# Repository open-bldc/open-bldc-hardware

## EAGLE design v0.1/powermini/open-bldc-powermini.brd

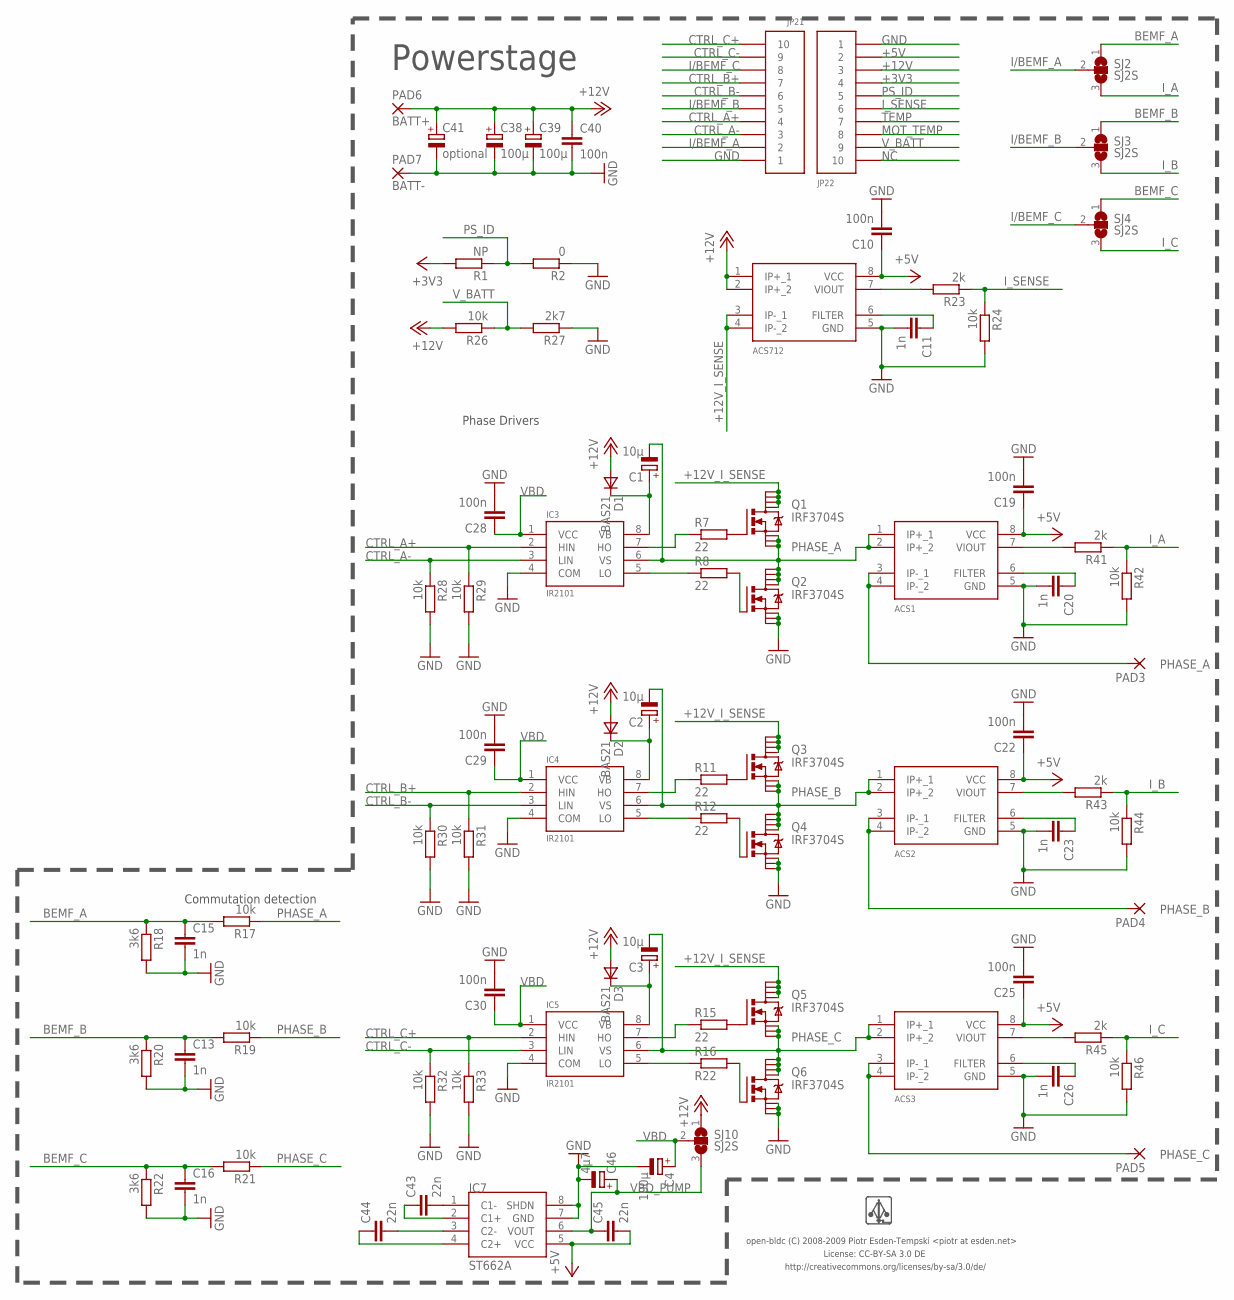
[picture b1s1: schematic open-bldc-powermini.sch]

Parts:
ACS1, ACS2, ACS3, ACS712: ACS712; SO8
C1, C2, C3: 10µ; A/3216-18R
C4, C38, C39: 100µ; D/7343-31R
C10, C19, C22, C25, C28, C29, C30, C40: 100n; C0603
C11, C13, C15, C16, C20, C23, C26: 1n; C0603
C41: optional; E5-6
C43, C44, C45: 22n; C0603
C46: 4µ7; A/3216-18R
D1, D2, D3: BAS21; SOT-23
IC3, IC4, IC5: IR2101; SO-8
IC7: ST662A; SO8
JP21, JP22: PIN_HDR_1.27MM_10; PIN_HDR_1.27MM_SMD_10
PAD3: PHASE_A; SMD2,54-5,08
PAD4: PHASE_B; SMD2,54-5,08
PAD5: PHASE_C; SMD2,54-5,08
PAD6: BATT+; SMD2,54-5,08
PAD7: BATT-; SMD2,54-5,08
Q1, Q2, Q3, Q4, Q5, Q6: IRF3704S; SO-08
R1: NP; R0603
R2: 0; R0603
R7, R8, R11, R12, R15: 22; R0603
R16: R22; R0603
R17, R19, R21, R24, R26, R28, R29, R30, R31, R32, R33, R42, R44, R46: 10k; R0603
R18, R20, R22: 3k6; R0603
R23, R41, R43, R45: 2k; R0603
R27: 2k7; R0603
SJ2, SJ3, SJ4, SJ10: SJ2S

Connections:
+3V3: JP22.4, R1.2
+5V: ACS1.8 (VCC), ACS2.8 (VCC), ACS3.8 (VCC), ACS712.8 (VCC), C10.1, C19.1, C22.1, C25.1, C45.2, IC7.5 (VCC), JP22.2
+12V: ACS712.1 (IP+_1), ACS712.2 (IP+_2), C38.+, C39.+, C40.1, C41.+, D1.3 (A), D2.3 (A), D3.3 (A), JP22.3, PAD6.1, R26.2, SJ10.1
+12V_I_SENSE: ACS712.3 (IP-_1), ACS712.4 (IP-_2), Q1.5 (D), Q1.6 (D), Q1.7 (D), Q1.8 (D), Q3.5 (D), Q3.6 (D), Q3.7 (D), Q3.8 (D), Q5.5 (D), Q5.6 (D), Q5.7 (D), Q5.8 (D)
BEMF_A: C15.1, R17.2, R18.1, SJ2.1
BEMF_B: C13.1, R19.2, R20.1, SJ3.1
BEMF_C: C16.1, R21.2, R22.1, SJ4.1
CTRL_A+: IC3.2 (HIN), JP21.4, R29.1
CTRL_A-: IC3.3 (LIN), JP21.3, R28.1
CTRL_B+: IC4.2 (HIN), JP21.7, R31.1
CTRL_B-: IC4.3 (LIN), JP21.6, R30.1
CTRL_C+: IC5.2 (HIN), JP21.10, R33.1
CTRL_C-: IC5.3 (LIN), JP21.9, R32.1
GND: ACS1.5 (GND), ACS2.5 (GND), ACS3.5 (GND), ACS712.5 (GND), C4.-, C10.2, C11.2, C13.2, C15.2, C16.2, C19.2, C20.2, C22.2, C23.2, C25.2, C26.2, C28.2, C29.2, C30.2, C38.-, C39.-, C40.2, C41.-, C46.-, IC3.4 (COM), IC4.4 (COM), IC5.4 (COM), IC7.7 (GND), IC7.8 (SHDN), JP21.1, JP22.1, PAD7.1, Q2.1 (S), Q2.2 (S), Q2.3 (S), Q4.1 (S), Q4.2 (S), Q4.3 (S), Q6.1 (S), Q6.2 (S), Q6.3 (S), R2.1, R18.2, R20.2, R22.2, R24.2, R27.1, R28.2, R29.2, R30.2, R31.2, R32.2, R33.2, R42.2, R44.2, R46.2
I/BEMF_A: JP21.2, SJ2.2
I/BEMF_B: JP21.5, SJ3.2
I/BEMF_C: JP21.8, SJ4.2
I_A: R41.1, R42.1, SJ2.3
I_B: R43.1, R44.1, SJ3.3
I_C: R45.1, R46.1, SJ4.3
I_PHASE_A: ACS1.3 (IP-_1), ACS1.4 (IP-_2), PAD3.1
I_PHASE_B: ACS2.3 (IP-_1), ACS2.4 (IP-_2), PAD4.1
I_PHASE_C: ACS3.3 (IP-_1), ACS3.4 (IP-_2), PAD5.1
I_SENSE: JP22.6, R23.1, R24.1
MOT_TEMP: JP22.8
unnamed: IC4.7 (HO), R11.1
unnamed: IC3.7 (HO), R7.1
unnamed: ACS712.7 (VIOUT), R23.2
unnamed: IC3.5 (LO), R8.1
unnamed: Q1.4 (G), R7.2
unnamed: C1.+, D1.1 (C), IC3.8 (VB)
unnamed: IC4.5 (LO), R12.1
unnamed: Q3.4 (G), R11.2
unnamed: Q5.4 (G), R15.2
unnamed: C2.+, D2.1 (C), IC4.8 (VB)
unnamed: Q6.4 (G), R16.2
unnamed: IC5.7 (HO), R15.1
unnamed: IC5.5 (LO), R16.1
unnamed: C3.+, D3.1 (C), IC5.8 (VB)
unnamed: ACS712.6 (FILTER), C11.1
unnamed: C43.2, IC7.1 (C1-)
unnamed: C44.2, IC7.3 (C2-)
unnamed: C43.1, IC7.2 (C1+)
unnamed: C44.1, IC7.4 (C2+)
unnamed: ACS1.6 (FILTER), C20.1
unnamed: ACS1.7 (VIOUT), R41.2
unnamed: ACS2.6 (FILTER), C23.1
unnamed: ACS2.7 (VIOUT), R43.2
unnamed: ACS3.6 (FILTER), C26.1
unnamed: ACS3.7 (VIOUT), R45.2
unnamed: Q2.4 (G), R8.2
unnamed: Q4.4 (G), R12.2
NC: JP22.10
PHASE_A: ACS1.1 (IP+_1), ACS1.2 (IP+_2), C1.-, IC3.6 (VS), Q1.1 (S), Q1.2 (S), Q1.3 (S), Q2.5 (D), Q2.6 (D), Q2.7 (D), Q2.8 (D), R17.1
PHASE_B: ACS2.1 (IP+_1), ACS2.2 (IP+_2), C2.-, IC4.6 (VS), Q3.1 (S), Q3.2 (S), Q3.3 (S), Q4.5 (D), Q4.6 (D), Q4.7 (D), Q4.8 (D), R19.1
PHASE_C: ACS3.1 (IP+_1), ACS3.2 (IP+_2), C3.-, IC5.6 (VS), Q5.1 (S), Q5.2 (S), Q5.3 (S), Q6.5 (D), Q6.6 (D), Q6.7 (D), Q6.8 (D), R21.1
PS_ID: JP22.5, R1.1, R2.2
TEMP: JP22.7
VBD: C4.+, C28.1, C29.1, C30.1, IC3.1 (VCC), IC4.1 (VCC), IC5.1 (VCC), SJ10.2
VBD_PUMP: C45.1, C46.+, IC7.6 (VOUT), SJ10.3
V_BATT: JP22.9, R26.1, R27.2

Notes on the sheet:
Phase Drivers
License: CC-BY-SA 3.0 DE
http://creativecommons.org/licenses/by-sa/3.0/de/
Commutation detection
open-bldc (C) 2008-2009 Piotr Esden-Tempski <piotr at esden.net>
Powerstage

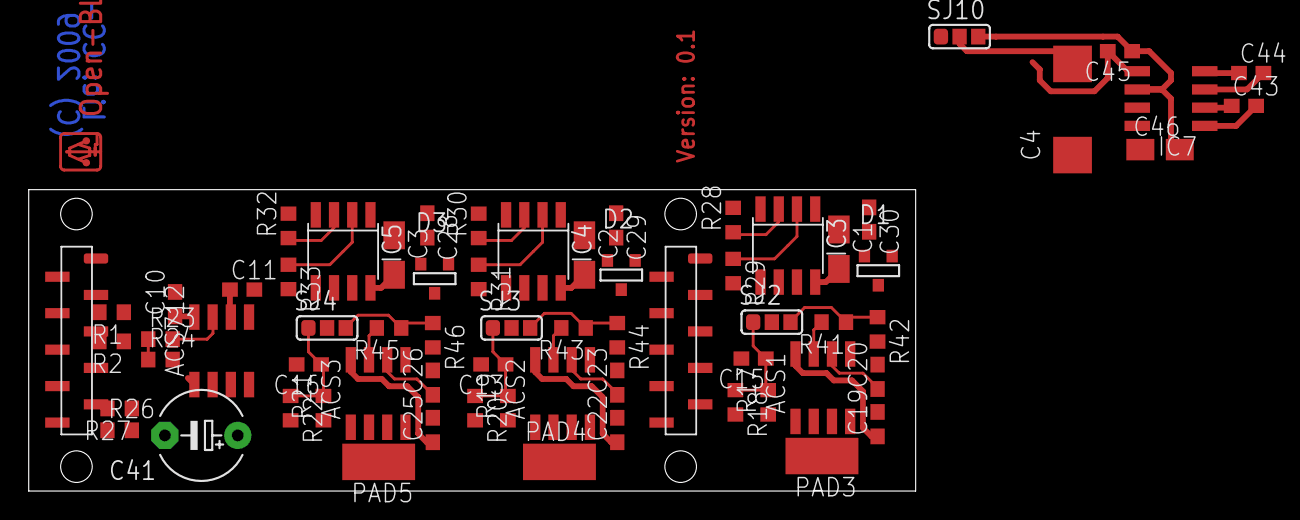
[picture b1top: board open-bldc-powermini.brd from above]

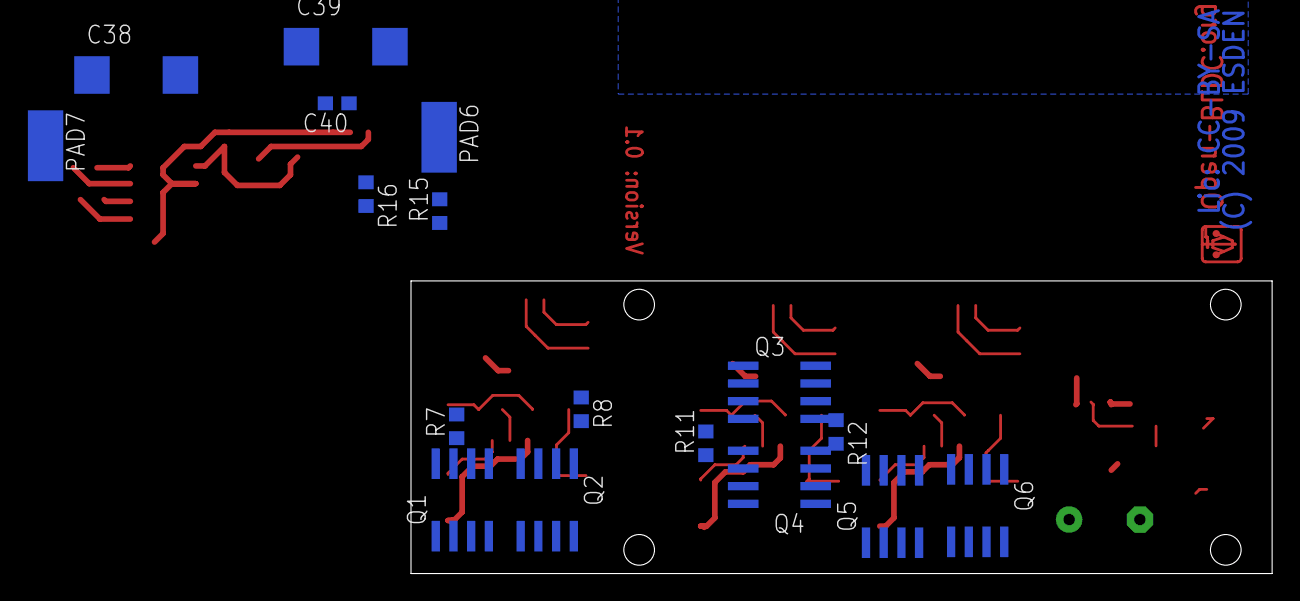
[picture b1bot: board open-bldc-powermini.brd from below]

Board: 2 copper layers, 61.8 x 21.0 mm, 84 parts (17 on the bottom side), 58 nets.

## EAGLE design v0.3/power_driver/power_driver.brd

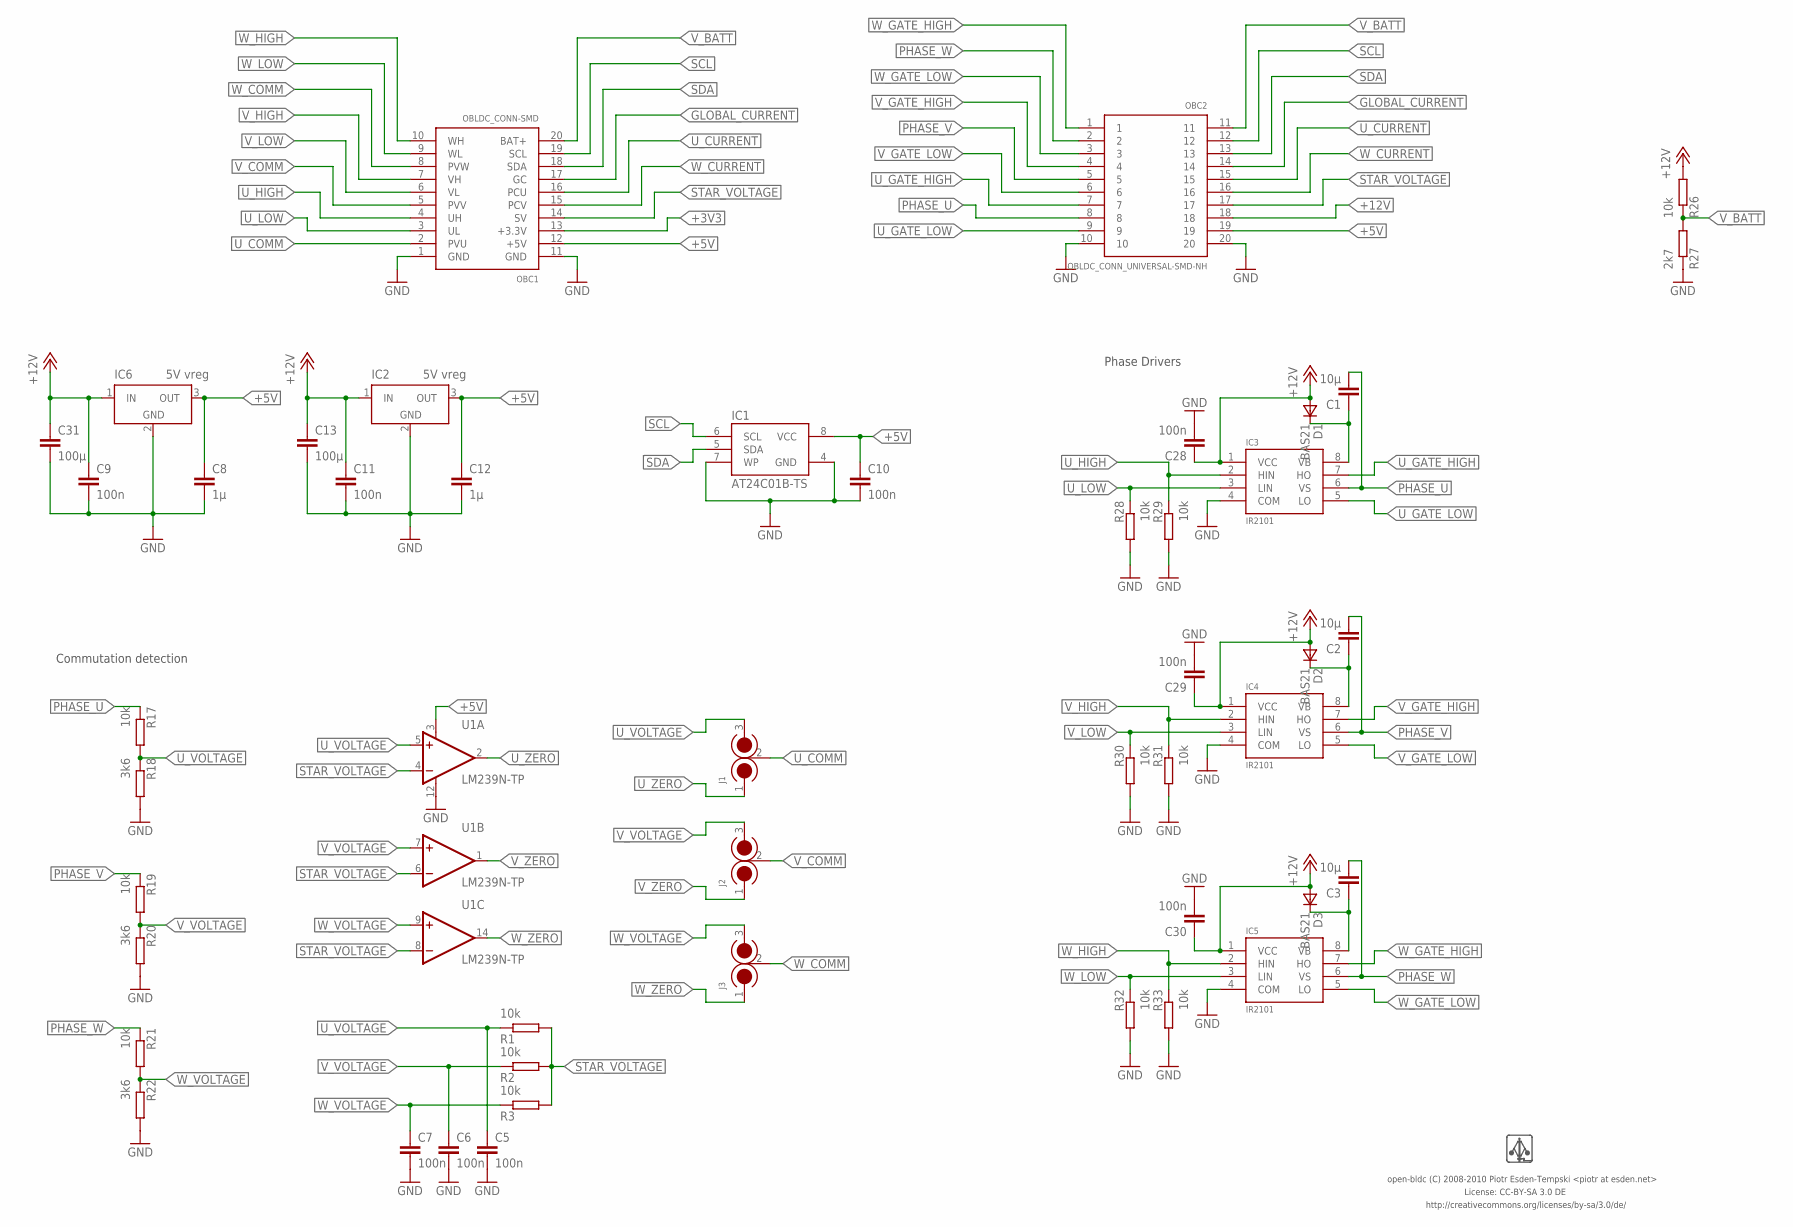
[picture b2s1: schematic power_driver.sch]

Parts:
C1, C2, C3: 10µ; 0603-CAP
C5, C6, C7, C9, C10, C11, C28, C29, C30: 100n; 0603-CAP
C8, C12: 1µ; 0603-CAP
C13, C31: 100µ; 0603-CAP
D1, D2, D3: BAS21; SOT-23
IC1: AT24C01B-TS; TSSOP8
IC2, IC6: 5V vreg; SOT223
IC3, IC4, IC5: IR2101; SO-8
J1, J2, J3: CIRC_JMP_2
OBC1: OBLDC_CONN-SMD; OBLDC_CONN_SMD
OBC2: OBLDC_CONN_UNIVERSAL-SMD-NH; OBLDC_CONN_SMD_NO_HOLES
R1, R2, R3, R17, R19, R21, R26, R28, R29, R30, R31, R32, R33: 10k; 0603-RES
R18, R20, R22: 3k6; 0603-RES
R27: 2k7; 0603-RES
U1: LM239N-TP; TSSOP_14
U$1: LOGO-NORM; LOGO

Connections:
+3V3: OBC1.13 (+3.3V)
+5V: C8.P$1 (1), C10.P$1 (1), C12.P$1 (1), IC1.8 (VCC), IC2.3 (OUT), IC6.3 (OUT), OBC1.12 (+5V), OBC2.19, U1.3 (V+)
+12V: C9.P$1 (1), C11.P$1 (1), C13.P$1 (1), C28.P$1 (1), C29.P$1 (1), C30.P$1 (1), C31.P$1 (1), D1.3 (A), D2.3 (A), D3.3 (A), IC2.1 (IN), IC3.1 (VCC), IC4.1 (VCC), IC5.1 (VCC), IC6.1 (IN), OBC2.18, R26.P$2 (2)
GLOBAL_CURRENT: OBC1.17 (GC), OBC2.14
GND: C5.P$2 (2), C6.P$2 (2), C7.P$2 (2), C8.P$2 (2), C9.P$2 (2), C10.P$2 (2), C11.P$2 (2), C12.P$2 (2), C13.P$2 (2), C28.P$2 (2), C29.P$2 (2), C30.P$2 (2), C31.P$2 (2), IC1.4 (GND), IC1.7 (WP), IC2.2 (GND), IC2.4 (GND), IC3.4 (COM), IC4.4 (COM), IC5.4 (COM), IC6.2 (GND), IC6.4 (GND), OBC1.1 (GND), OBC1.11 (GND), OBC2.10, OBC2.20, R18.P$2 (2), R20.P$2 (2), R22.P$2 (2), R27.P$1 (1), R28.P$2 (2), R29.P$2 (2), R30.P$2 (2), R31.P$2 (2), R32.P$2 (2), R33.P$2 (2), U1.12 (V-)
unnamed: C1.P$1 (1), D1.1 (C), IC3.8 (VB)
unnamed: C2.P$1 (1), D2.1 (C), IC4.8 (VB)
unnamed: C3.P$1 (1), D3.1 (C), IC5.8 (VB)
PHASE_U: C1.P$2 (2), IC3.6 (VS), OBC2.8, R17.P$1 (1)
PHASE_V: C2.P$2 (2), IC4.6 (VS), OBC2.5, R19.P$1 (1)
PHASE_W: C3.P$2 (2), IC5.6 (VS), OBC2.2, R21.P$1 (1)
SCL: IC1.6 (SCL), OBC1.19 (SCL), OBC2.12
SDA: IC1.5 (SDA), OBC1.18 (SDA), OBC2.13
STAR_VOLTAGE: OBC1.14 (SV), OBC2.17, R1.P$2 (2), R2.P$2 (2), R3.P$2 (2), U1.4 (-IN), U1.6 (-IN), U1.8 (-IN)
U_COMM: J1.2, OBC1.2 (PVU)
U_CURRENT: OBC1.16 (PCU), OBC2.15
U_GATE_HIGH: IC3.7 (HO), OBC2.7
U_GATE_LOW: IC3.5 (LO), OBC2.9
U_HIGH: IC3.2 (HIN), OBC1.4 (UH), R29.P$1 (1)
U_LOW: IC3.3 (LIN), OBC1.3 (UL), R28.P$1 (1)
U_VOLTAGE: C5.P$1 (1), J1.3, R1.P$1 (1), R17.P$2 (2), R18.P$1 (1), U1.5 (+IN)
U_ZERO: J1.1, U1.2 (OUT)
V_BATT: OBC1.20 (BAT+), OBC2.11, R26.P$1 (1), R27.P$2 (2)
V_COMM: J2.2, OBC1.5 (PVV)
V_GATE_HIGH: IC4.7 (HO), OBC2.4
V_GATE_LOW: IC4.5 (LO), OBC2.6
V_HIGH: IC4.2 (HIN), OBC1.7 (VH), R31.P$1 (1)
V_LOW: IC4.3 (LIN), OBC1.6 (VL), R30.P$1 (1)
V_VOLTAGE: C6.P$1 (1), J2.3, R2.P$1 (1), R19.P$2 (2), R20.P$1 (1), U1.7 (+IN)
V_ZERO: J2.1, U1.1 (OUT)
W_COMM: J3.2, OBC1.8 (PVW)
W_CURRENT: OBC1.15 (PCV), OBC2.16
W_GATE_HIGH: IC5.7 (HO), OBC2.1
W_GATE_LOW: IC5.5 (LO), OBC2.3
W_HIGH: IC5.2 (HIN), OBC1.10 (WH), R33.P$1 (1)
W_LOW: IC5.3 (LIN), OBC1.9 (WL), R32.P$1 (1)
W_VOLTAGE: C7.P$1 (1), J3.3, R3.P$1 (1), R21.P$2 (2), R22.P$1 (1), U1.9 (+IN)
W_ZERO: J3.1, U1.14 (OUT)

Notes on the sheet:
Phase Drivers
License: CC-BY-SA 3.0 DE
http://creativecommons.org/licenses/by-sa/3.0/de/
Commutation detection
open-bldc (C) 2008-2010 Piotr Esden-Tempski <piotr at esden.net>

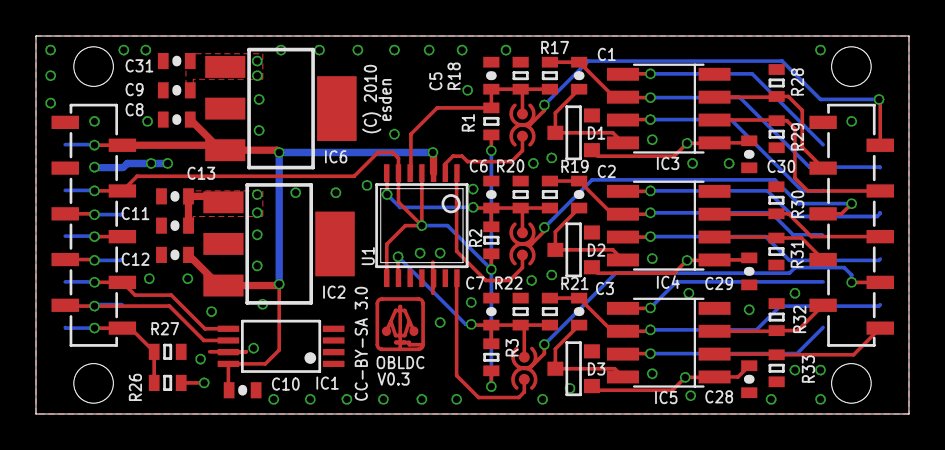
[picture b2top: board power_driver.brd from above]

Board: 4 copper layers, 48.5 x 21.0 mm, 49 parts (1 on the bottom side), 37 nets.

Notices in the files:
v0.1/powermini/open-bldc-powermini.brd:
(C) 2009 ESDEN
Lic: CC-BY-SA
v0.3/power_driver/power_driver.brd:
(C) 2010
